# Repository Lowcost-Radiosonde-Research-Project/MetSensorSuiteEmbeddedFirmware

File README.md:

# Met Pico Sensor Suite - Firmware Skeleton

Status as of latest revision. Every module now has a real
implementation - BMI330's carries a significant caveat (see below and
its module docstring) since its register map is unverified.

## File layout

| File              | Status | Notes |
|-------------------|--------|-------|
| `config.py`       | Real   | All pins/addresses/constants in one place. Several `TODO`s remain. |
| `packet.py`       | Real   | Fixed-width binary record format (`PACKET_FORMAT = "<I15fBBBB"`, 68 bytes). |
| `bme280.py`       | Real   | Full Bosch compensation formulas, forced-mode reads. I2C bus 1. |
| `rtd_ads1115.py`  | Real   | Ratiometric RTD read + Callendar-Van Dusen (T >= 0 C only). I2C bus 1. |
| `ms5611.py`       | Real   | PROM calibration + 1st/2nd-order temp/pressure compensation. I2C bus 2. |
| `bmi330.py`       | **Unverified** | Register map guessed from the related BMI323; may not function as intended - see caveat below. I2C bus 2. |
| `gps_neo_m9n.py`  | Real   | NMEA GGA parsing: lat/lon/alt/num_sats/UTC time. |
| `sd_logger.py`    | Real   | Mounts SD, appends `packet.pack_record()` output, periodic flush. |
| `imet_packet.py`  | Real   | Builds the 38-byte iMet-1-RSB GPS+PTU-enhanced downlink frame + CRC-16. |
| `link_uart.py`    | Real   | Frames and sends one 38-byte iMet frame per cycle to the RF Pico over UART. |
| `main.py`         | Real   | Two I2C buses, SD log + iMet frame to RF Pico link, per-sensor fault isolation. |

Every sensor module exposes `init_<name>(i2c, addr)` returning an
object with a `read()` method, and `main.py` wraps each init in
`try/except (OSError, ValueError)` and each read in `try/except
OSError` (the only error read() can raise) so one bad/missing sensor
doesn't take down the loop or the log - it just logs NAN for that field
and a `[WARN]` line to the console.

## Bus layout

- **I2C bus 1** (`I2C1*`): ADS1115 (RTD) + BME280
- **I2C bus 2** (`I2C2*`): MS5611 + BMI330
- **UART** (`GPS_UART_*`): NEO-M9N GPS
- **UART** (`LINK_UART_*`): outbound link to the RF Pico, one framed
  38-byte iMet-1-RSB frame per cycle (see `imet_packet.py` /
  `link_uart.py`)
- **SPI** (`SD_*`): SD card

All pin numbers above are placeholders pending the Tuesday wiring
session - see the `TODO`s in `config.py`.

## BMI330 caveat - documentation lacking, driver may not work as intended

`bmi330.py` is written against the BMI323's register map (a related
Bosch part) because verified BMI330-specific register documentation
wasn't available when this was written. The register addresses,
ACC_CONF/GYR_CONF bitfield values, and full-scale range assumptions are
all unverified guesses. **The driver may run without raising any error
and still return meaningless numbers.**

On Tuesday, `init_bmi330()` will print whatever it reads from the
assumed CHIP_ID register (0x00) as a diagnostic - note that value down.
If accel/gyro readings look like noise, sit constant, or are far
outside physical range (accelerometer magnitude should be close to 1g
at rest), the register map guess is wrong and `bmi330.py` needs
revisiting against real BMI330 documentation (Bosch's BMI3 Sensor API
repo is the best starting point once it covers BMI330). This isn't
blocking for Wednesday - BMI330 isn't part of that test.

## Field naming convention

`packet.FIELD_NAMES` prefixes every field with the sensor that owns it
(`bme280_*`, `ms5611_*`, `rtd_*`, `bmi330_*`, `gps_*`). BMI330 fields
are in milli-g / milli-deg/s (`_mg` / `_mdps`) rather than g / deg-per-s
- worth keeping in mind when the real BMI330 driver is written, since
the conversion from raw counts will need to land in those units.

The GPS record has `gps_num_sats` plus `gps_hour`/`gps_minute`/
`gps_second` (UTC time of fix), but no fix-type field - `gps.read()`
returns a 7-tuple `(lat, lon, alt, num_sats, hour, minute, second)`.
Position/altitude are NAN and the satellite/time fields are
`NO_DATA_U8` until a checksum-valid GGA sentence with a non-zero fix
quality has been parsed. If you want fix-quality (e.g. for
SondeHub-style reporting) added too, that's a small change to
`packet.py` (one more `B` field) and `gps_neo_m9n.py`'s `_parse_gga()`.

## iMet-1-RSB downlink frame

Each cycle, after the SD record is written, `main.py` builds a
separate 38-byte frame via `imet_packet.pack_frame()` - a GPS Data
Packet (`PKT_ID=0x02`, 18 bytes) immediately followed by a PTU
(enhanced) Data Packet (`PKT_ID=0x04`, 20 bytes), each with its own
CRC-16, matching InterMet's "Appendix A - Binary Radiosonde Packet
Definition" as decoded by `imet1rsb`. This frame - not the `packet.py`
record - is what gets sent over `link_uart` to the RF Pico for AFSK
modulation; `packet.py` stays SD-only.

Current sensor -> iMet field mapping (set in `main.py`, easy to
change - it's just which `record[...]` value is passed to which
`imet_packet` keyword argument):

| iMet field | Source | Notes |
|---|---|---|
| GPS lat/lon/alt/num_sats/hour/min/sec | `gps_*` record fields | real NMEA GGA parsing; NAN/NO_DATA until a fix is acquired |
| P (pressure) | `ms5611_pressure_hpa` | **TODO**: confirm vs. BME280 as the primary pressure source |
| T (primary temp) | `bme280_temp_c` | |
| U (humidity) | `bme280_humidity_pct` | |
| Vbat | hardcoded NAN | **TODO**: no battery-voltage sensing exists yet (new ADC channel) |
| Tint (internal temp) | `bme280_temp_c` | **TODO**: currently duplicates T - confirm intent |
| Tpr (probe temp) | `rtd_temp_c` | |
| Tu (aux temp) | hardcoded NAN | **TODO**: no mapping defined - InterMet's intended use of this field is unclear |

All of the NAN/sentinel placeholders above pack safely (verified in
`imet_packet.py`'s `_scaled_*`/`_encode_altitude` helpers - they map
NAN to the field's "no data" value rather than raising), so the frame
is well-formed even with everything still stubbed.

## Before Tuesday (no hardware needed)

- [ ] Get a copy of `sdcard.py` onto the board. Easiest path in
      Thonny/REPL: `import mip; mip.install("sdcard")`. This is the
      standard MicroPython SD-over-SPI block driver - `sd_logger.py`
      imports it as `sdcard`.
- [ ] Skim `config.py` for the `TODO` items - nothing blocks you from
      reading the code now, but these are the values you'll set Tuesday.

## Tuesday, once hardware is in hand

- [ ] Update `config.py` pin numbers for both I2C buses, SPI (SD), GPS
      UART, the RF Pico link UART, and `REGULATOR_EN_PIN` (LM2596 3.3V
      rail enable) to match actual wiring.
- [ ] Confirm `RTD_MUX` / `REF_MUX` (which ADS1115 differential pair is
      the RTD vs. the reference resistor) and `ADS1115_GAIN` (PGA
      setting), based on the RTD interface board.
- [ ] Confirm `MS5611_I2C_ADDR` and `BMI330_I2C_ADDR` once those boards
      are wired. MS5611 and GPS now have real drivers, so a wrong
      address will surface as `[WARN] ... init failed` from
      `_safe_init` rather than silently logging NaN.
- [ ] For BMI330: note the `[INFO] BMI330 CHIP_ID register read as
      0x..` line at startup and sanity-check accel/gyro readings
      against the caveat above - this driver's register map is a
      guess.
- [ ] Run `main.py`. With only BME280 + RTD wired, expect `[WARN]`
      lines at startup for MS5611/BMI330/GPS init or SD mount (if not
      present) - that's expected, the loop should keep running and
      print live T/P/RH/RTD values once per second.

## Wednesday (storm chase)

The console line each cycle:

```
t=   12345ms  T= 23.45C  P=1006.32hPa  RH= 45.2%  RTD= 23.10C
```

gives a live sanity check that BME280 and RTD agree roughly with each
other and with ambient conditions. The SD card (if mounted) accumulates
`PACKET_SIZE`-byte (68-byte) binary records in `/sd/metlog.bin` - decode
with `packet.unpack_record()` in a small post-processing script, reading
`PACKET_SIZE` bytes at a time.

## Known gaps / next steps

- RTD conversion only handles T >= 0 C (Callendar-Van Dusen quadratic
  inversion). The sub-zero cubic-term inversion needs to be added before
  the actual flight.
- BMI330 is unverified - see the dedicated caveat section above and
  `bmi330.py`'s module docstring before trusting any IMU data.
- `link_uart.py` now sends a 38-byte iMet frame instead of the
  65-byte `packet.py` record - see "iMet-1-RSB downlink frame" above
  for the sensor mapping and its open TODOs (Vbat sensing, GPS UTC
  time, P/Tint/Tu assignment).
- `imet_packet.py` matches the field layout and CRC algorithm from
  `imet1rsb.c`'s source, but hasn't been cross-checked byte-for-byte
  against a compiled run of that decoder yet. Worth doing once there's
  a spare moment - compile `imet1rsb.c`, feed it a known frame, and
  confirm its `crc16()` agrees with `imet_packet.crc16()`.
- The RF Pico's receive-side parser for `link_uart`'s frame format
  (sync bytes + length + checksum) doesn't exist yet - that's firmware
  for the other board, out of scope here, but the frame format is
  documented at the top of `link_uart.py` so it can be matched.
- `main.py` currently runs everything on a single core via a simple
  fixed-interval loop. If SD writes, link UART sends, or sensor reads
  start causing timing jitter once everything is real, revisit
  splitting acquisition and logging across the two cores with
  `_thread`.

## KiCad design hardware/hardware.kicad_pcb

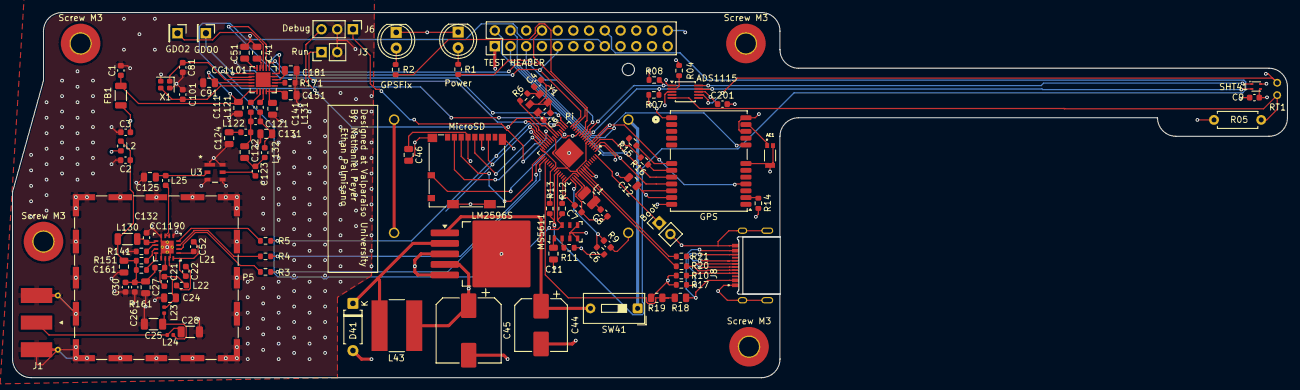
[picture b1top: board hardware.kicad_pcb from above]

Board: 4 copper layers, 206.0 x 59.0 mm, 114 parts (1 on the bottom side), 86 nets.

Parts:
ADS1115: ADS1115IDGS; TSSOP-10_3x3mm_P0.5mm
AE1: W3011; XDCR_W3011
B41: 1079; 1079_KEY
Boot: J_BOOT; PinHeader_1x02_P2.54mm_Vertical
C1, C30: 1uF; C_0603_1608Metric
C2: 10uF; C_0603_1608Metric
C3: 220pF; C_0603_1608Metric
C4, C5: 15p; C_0603_1608Metric
C6, C7, C8: 4.7u; C_0603_1608Metric
C9, C201: 10 uF; C_0603_1608Metric
C11, C12, C46: 0.1 uF; C_0805_2012Metric
C21, C26, C123: 47pF; C_0603_1608Metric
C22, C52, C81: 12pF; C_0603_1608Metric
C24: 3.3pF; C_0805_2012Metric
C25: 7.5pF; C_1206_3216Metric
C27: 1nF; C_0805_2012Metric
C28: DNP; C_1206_3216Metric
C41, C51, C91, C111, C141, C151, C181: 100nF; C_0805_2012Metric
C44: 180 uF; CP_Elec_8x6.7
C45: 330/35 uF/V; CP_Elec_10x10
C101, C132: 15pF; C_0603_1608Metric
C121: 1.9pF; C_0603_1608Metric
C122, C131: 1.5pF; C_0805_2012Metric
C124: 100pF; C_0805_2012Metric
C125: 0.8pF; C_0805_2012Metric
C161: 27pF; C_0805_2012Metric
CC1101: CC1101; Texas_RGP0020H_VQFN-20-1EP_4x4mm_P0.5mm_EP2.4x2.4mm_Thermal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
CC1190: CC1190; RGV0016A
D41: 1N5820; D_A-405_P7.62mm_Horizontal
FB1: FerriteBead; L_1206_3216Metric
GDO0, GDO2: TestPoint; PinHeader_1x01_P2.54mm_Vertical
GPS: NEO-M9N; ublox_NEO
GPSFix: Blue LED; LED_D5.0mm
J1: SMA; SMA_Molex_73251-1153_EdgeMount_Horizontal
J3: J_RUN; PinHeader_1x02_P2.54mm_Vertical
J6: DEBUG; PinHeader_1x03_P2.54mm_Vertical
J8: GSB1C4621DS1HR; AMPHENOL_GSB1C4621DS1HR
L1: 3.3u; L_1008_2520Metric
L2: 11nH; L_0603_1608Metric
L21: 22nH; L_0603_1608Metric
L22: 7.5nH; L_0603_1608Metric
L23: 2.9nH; L_0402_1005Metric
L24: 9.1nH; L_0402_1005Metric
L25: 10nH; L_0603_1608Metric
L43: 33 uH; L_Bourns-SRN8040_8x8.15mm
L121, L131: 12nH; L_0603_1608Metric
L122, L132: 18nH; L_0603_1608Metric
L130: 1.5nH; L_1206_3216Metric
LM2596S: LM2596S-3.3; TO-263-5_TabPin3
MS5611: MS5611-01BA; LGA-8_3x5mm_P1.25mm
MicroSD: Micro_SD_Card_Det1; microSD_HC_Molex_104031-0811
P5: BMI-S-205-C; Laird_Technologies_BMI-S-203-F_26.21x26.21mm
Pi: RP2354A; QFN-60-1EP_7x7mm_P0.4mm_EP3.4x3.4mm
Power: Red LED; LED_D5.0mm
R1, R2: 330; R_0603_1608Metric
R3, R4, R04, R5: 10K; R_0603_1608Metric
R05: 10K OHM 0.1% 0.4W AXIAL; R_Axial_DIN0207_L6.3mm_D2.5mm_P7.62mm_Horizontal
R6: 1K; R_0603_1608Metric
R07, R08, R12, R13, R15, R16: 4.7k; R_0603_1608Metric
R9: 33; R_0603_1608Metric
R10, R17: 5.1K; R_0603_1608Metric
R11, R14: 10k; R_0603_1608Metric
R18, R19: 27K; R_0805_2012Metric
R20, R21: 27; R_0603_1608Metric
R141: 3.3k; R_0603_1608Metric
R151: 47; R_0603_1608Metric
R161: 10; R_0603_1608Metric
R171: 56K; R_0603_1608Metric
RT1: PPG102JA
SHT41: SHT41-AD1B-R3; SHT4X
SW41: SW_SPST; SW_DIP_SPSTx01_Slide_9.78x4.72mm_W7.62mm_P2.54mm
Screw M3, Screw M3#2, Screw M3#3, Screw M3#4: MountingHole_3.2mm_M3_Pad_TopBottom
TEST HEADER: Test Header; PinHeader_2x12_P2.54mm_Vertical
U3: B39921B3588U410; B39162B3522U410_TDK-L
X1: 26.000 MHz; Crystal_SMD_2016-4Pin_2.0x1.6mm
Y1: CX3225SB12000D0GZJC1; OSCCC320X250X60N

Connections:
GPS_EXT_INT: GPS.4 (EXTINT), Pi.5 (GPIO3), TEST HEADER.5
GPS_RESET_N: GPS.8 (~RESET), Pi.4 (GPIO2), TEST HEADER.4
GPS_RX: GPS.20 (TXD/SPI_MISO), Pi.3 (GPIO1), TEST HEADER.3
GPS_TX: GPS.21 (RXD/SPI_MOSI), Pi.2 (GPIO0), TEST HEADER.2
HGM: Pi.33 (GPIO21), R3.2, TEST HEADER.17
I2C0_SCL: ADS1115.10 (SCL), Pi.8 (GPIO5), R08.2, SHT41.1 (SDA), TEST HEADER.7
I2C0_SDA: ADS1115.9 (SDA), Pi.7 (GPIO4), R07.2, SHT41.2 (SCL), TEST HEADER.6
I2C1_SCL: MS5611.8 (SCLK), Pi.40 (GPIO26/ADC0), R13.1, TEST HEADER.16
I2C1_SDA: MS5611.7 (SDI/SDA), Pi.41 (GPIO27/ADC1), R12.1, TEST HEADER.15
LED_GPSF: Pi.10 (GPIO7), R2.2
LED_PWR: Pi.9 (GPIO6), R1.2
LNA_EN: Pi.32 (GPIO20), R4.2, TEST HEADER.18
unnamed: B41.2, B41.4
unnamed: C4.2, R6.1, Y1.3
unnamed: C21.1, C24.1, L22.1, L23.1
unnamed: C22.1, L22.2
unnamed: C25.1, L23.2, L24.1
unnamed: C121.1, C122.1, L121.1, L122.2
unnamed: C121.2, C131.1, L131.1, L132.2
unnamed: C122.2, C123.1, L132.1
unnamed: C123.2, U3.5
unnamed: C124.1, L122.1
unnamed: C125.1, L25.2, U3.2
unnamed: C2.1, C26.1, C27.1, C30.1, C161.1, L2.1, L21.1, L130.1, R151.1, R161.1
unnamed: Power.2 (A), R1.1
unnamed: GPSFix.2 (A), R2.1
unnamed: D41.1 (K), L43.2, LM2596S.2 (OUT)
unnamed: C28.1, J1.1 (In), L24.2
unnamed: J8.A5 (CC1), R10.1
unnamed: J8.B5 (CC2), R17.1
unnamed: J8.A7 (DN1), J8.B7 (DN2), R20.1
unnamed: J8.A6 (DP1), J8.B6 (DP2), R21.1
unnamed: J8.A4_B9 (VBUS_A), J8.B4_A9 (VBUS_B), R18.1
unnamed: ADS1115.5 (AIN1), R05.2, RT1.1 (IN)
unnamed: B41.1, SW41.1 (A)
unnamed: C44.1, LM2596S.1 (VIN), SW41.2 (B)
unnamed: C6.2, Pi.46 (VREG_AVDD), R9.1
unnamed: CC1190.14 (BIAS), R141.2
unnamed: CC1190.6 (HGM), R3.1
unnamed: CC1190.7 (LNA_EN), R4.1
unnamed: C52.2, CC1190.5 (LNA_IN)
unnamed: CC1190.10 (LNA_OUT), CC1190.11 (PA_IN), L25.1
unnamed: CC1190.8 (PA_EN), R5.1
unnamed: C21.2, CC1190.2 (PA_OUT), L21.2
unnamed: C22.2, C52.1, CC1190.4 (TR_SW)
unnamed: C132.1, CC1190.13 (VDD_LNA), L130.2
unnamed: CC1190.16 (VDD_PA1), R161.2
unnamed: CC1190.15 (VDD_PA2), R151.2
unnamed: ADS1115.2 (ALERT/RDY), R04.2
unnamed: C51.1, CC1101.5 (DCOUPL)
unnamed: C1.1, C41.1, C91.1, C111.1, C141.1, C151.1, C181.1, CC1101.4 (DVDD), CC1101.9 (AVDD), CC1101.11 (AVDD), CC1101.14 (AVDD), CC1101.15 (AVDD), CC1101.18 (DGUARD), FB1.1
unnamed: CC1101.6 (GDO0), GDO0.1 (1_1)
unnamed: CC1101.3 (GDO2), GDO2.1 (1_1)
unnamed: CC1101.17 (RBIAS), R171.1
unnamed: CC1101.13 (RF_N), L131.2
unnamed: CC1101.12 (RF_P), L121.2
unnamed: C81.1, CC1101.8 (XOSC_Q1), X1.1
unnamed: C101.1, CC1101.10 (XOSC_Q2), X1.2
unnamed: MS5611.2 (PS), R11.1
unnamed: GPS.2 (D_SEL), R14.2
unnamed: AE1.1, GPS.11 (RF_IN)
unnamed: GPS.19 (SCL/SPI_CLK), R16.2
unnamed: GPS.18 (SDA/~SPI_CS), R15.2
PA_EN: Pi.18 (GPIO14), R5.2, TEST HEADER.12
QSPI_SS: Boot.1, Pi.60 (~QSPI_SS)
RUN: J3.1, Pi.26 (RUN)
SD_CSn: MicroSD.2 (DAT3/CD), Pi.28 (GPIO17), TEST HEADER.21
SD_DETECT: MicroSD.9 (DET), Pi.19 (GPIO15), TEST HEADER.23
SD_RX: MicroSD.7 (DAT0), Pi.27 (GPIO16), TEST HEADER.22
SD_SCK: MicroSD.5 (CLK), Pi.29 (GPIO18), TEST HEADER.20
SD_TX: MicroSD.3 (CMD), Pi.31 (GPIO19), TEST HEADER.19
SPI1_CSn: CC1101.7 (CSN), Pi.17 (GPIO13), TEST HEADER.11
SPI1_RX: CC1101.2 (SO), Pi.16 (GPIO12), TEST HEADER.10
SPI1_SCK: CC1101.1 (SCLK), Pi.14 (GPIO10), TEST HEADER.8
SPI1_TX: CC1101.20 (SI), Pi.15 (GPIO11), TEST HEADER.9
SWCLK: J6.1, Pi.24 (SWCLK)
SWDIO: J6.3, Pi.25 (SWDIO)
USB_DM: Pi.51 (USB_DM), R20.2
USB_DP: Pi.52 (USB_DP), R21.2
VBUS: Pi.34 (GPIO22), R18.2, R19.1
VREG_FB: C8.2, L1.1, Pi.6 (DVDD), Pi.23 (DVDD), Pi.39 (DVDD), Pi.50 (VREG_FB)
VREG_LX: L1.2, Pi.48 (VREG_LX)
VREG_PGND: ADS1115.1 (ADDR), ADS1115.3 (GND), ADS1115.7 (AIN3), AE1.2, AE1.3, B41.3, Boot.2, C1.2, C2.2, C3.2, C4.1, C5.1, C6.1, C7.1, C8.1, C9.2, C11.2, C12.2, C24.2, C25.2, C26.2, C27.2, C28.2, C30.2, C41.2, C44.2, C45.2, C46.2, C51.2, C81.2, C91.2, C101.2, C111.2, C124.2, C125.2, C131.2, C132.2, C141.2, C151.2, C161.2, C181.2, C201.2, CC1101.16 (GND), CC1101.19 (GND), CC1101.21 (EPAD), CC1190.1 (GND), CC1190.3 (GND), CC1190.9 (GND), CC1190.12 (GND), CC1190.17 (GND), D41.2 (A), GPS.7 (VDD_USB), GPS.10 (GND), GPS.12 (GND), GPS.13 (GND), GPS.24 (GND), GPSFix.1 (K), J1.2 (Ext), J3.2, J6.2, J8.A1_B12 (GND_A), J8.B1_A12 (GND_B), J8.SH1 (SHIELD), J8.SH2 (SHIELD__1), J8.SH3 (SHIELD__2), J8.SH4 (SHIELD__3), LM2596S.3 (GND), LM2596S.5 (~ON/OFF), MS5611.3 (GND), MS5611.4 (CSB), MS5611.5 (CSB), MicroSD.6 (VSS), MicroSD.SH (SHIELD), P5.1 (Shield_1), Pi.47 (VREG_PGND), Pi.61 (GND), Power.1 (K), R10.2, R17.2, R19.2, R141.1, R171.2, RT1.2 (OUT), SHT41.4 (VSS), TEST HEADER.13, TEST HEADER.14, TEST HEADER.24, U3.1, U3.3, U3.4, U3.6, Y1.2 (GND), Y1.4 (GND__1)
VREG_VIN: ADS1115.8 (VDD), C3.1, C7.2, C9.1, C11.1, C12.1, C45.1, C46.1, C201.1, FB1.2, GPS.22 (V_BCKP), GPS.23 (VCC), L2.2, L43.1, LM2596S.4 (FB), MS5611.1 (VDD), MicroSD.4 (VDD), Pi.1 (IOVDD), Pi.11 (IOVDD), Pi.20 (IOVDD), Pi.30 (IOVDD), Pi.38 (IOVDD), Pi.44 (ADC_AVDD), Pi.45 (IOVDD), Pi.49 (VREG_VIN), Pi.53 (USB_OTP_VDD), Pi.54 (QSPI_IOVDD), R04.1, R05.1, R07.1, R08.1, R9.2, R11.2, R12.2, R13.2, R14.1, R15.1, R16.1, SHT41.3 (VDD), TEST HEADER.1
XIN: C5.2, Pi.21 (XIN), Y1.1
XOUT: Pi.22 (XOUT), R6.2

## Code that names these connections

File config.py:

"""Hardware configuration constants for the Met Pico sensor suite.

Centralizes pin assignments, bus addresses, ADC channel mappings, and
calibration constants so that hardware changes only require edits in
this file. Values marked TODO are placeholders pending hardware
confirmation and must be updated before flight.

Author: Nathaniel Peyer
Date: 06-14-2026
"""

# I2C bus 1: ADS1115 (RTD interface) and BME280.
I2C1 = 0
I2C1_SDA_PIN = 0
I2C1_SCL_PIN = 1
I2C1_FREQ_HZ = 400000

# I2C bus 2: MS5611 and BMI330.
# TODO: confirm BMI330 is on I2C (vs SPI) once hardware is finalized -
# this assumes both remaining I2C sensors share the second bus.
I2C2 = 1
I2C2_SDA_PIN = 2
I2C2_SCL_PIN = 3
I2C2_FREQ_HZ = 400000

# BME280 (temperature / pressure / humidity).
BME280_I2C_ADDR = 0x76

# MS5611 (high-resolution pressure / temperature).
# TODO: confirm address (0x77 if CSB tied high, 0x76 if tied low).
MS5611_I2C_ADDR = 0x77

# BMI330 (6-axis IMU).
# TODO: confirm address and bus once hardware is finalized.
BMI330_I2C_ADDR = 0x68

# ADS1115 (4-wire PT1000 RTD interface).
ADS1115_I2C_ADDR = 0x48

# ADS1115 MUX[2:0] codes (config register bits 14:12) select which
# differential pair is measured. The ADS1115 only supports four
# differential combinations:
#   0b000 -> AIN0 - AIN1
#   0b001 -> AIN0 - AIN3
#   0b010 -> AIN1 - AIN3
#   0b011 -> AIN2 - AIN3
# TODO: confirm which pair carries the RTD sense voltage and which
# carries the reference resistor once the RTD interface board wiring
# is finalized.
RTD_MUX = 0b000
REF_MUX = 0b011

# ADS1115 PGA[2:0] code (config register bits 11:9) sets the full-scale
# input range:
#   0 -> +/-6.144V   1 -> +/-4.096V   2 -> +/-2.048V
#   3 -> +/-1.024V   4 -> +/-0.512V   5 -> +/-0.256V
# TODO: confirm once excitation current and the expected voltage range
# across the RTD and reference resistor are known.
ADS1115_GAIN = 1

RTD_REF_RESISTANCE_OHMS = 10000.0

# Callendar-Van Dusen coefficients for PT1000 (IEC 60751), valid for
# T >= 0 deg C.
RTD_R0_OHMS = 1000.0
RTD_CVD_A = 3.9083e-3
RTD_CVD_B = -5.775e-7

# NEO-M9N GPS (UART, NMEA 0183).
GPS_UART_ID = 1
GPS_UART_TX_PIN = 4
GPS_UART_RX_PIN = 5
GPS_UART_BAUD_RATE = 9600

# UART link to the RF Pico - one packet.pack_record() payload, framed
# by link_uart.send_record(), is sent each sample cycle.
# TODO: confirm pins and baud rate once the inter-Pico wiring is set.
LINK_UART_ID = 0
LINK_UART_TX_PIN = 12
LINK_UART_RX_PIN = 13
LINK_UART_BAUD_RATE = 115200

# SD card (SPI).
SD_SPI_ID = 0
SD_SCK_PIN = 18
SD_MOSI_PIN = 19
SD_MISO_PIN = 16
SD_CS_PIN = 17
SD_MOUNT_POINT = "/sd"
SD_LOG_FILENAME = "/sd/metlog.bin"

# LM2596 switching regulator that supplies the 3.3V sensor rail. This
# GPIO must be driven high before any I2C/UART sensor transaction will
# succeed - main() asserts it first thing, then waits
# REGULATOR_ENABLE_DELAY_MS for the rail to settle.
# TODO: confirm pin number once wiring is finalized.
REGULATOR_EN_PIN = 14
REGULATOR_ENABLE_DELAY_MS = 50

# Sampling and logging cadence.
SAMPLE_INTERVAL_MS = 1000
SD_FLUSH_INTERVAL_SAMPLES = 5

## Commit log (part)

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2026-06-14 Created the repo for the project and set up admin files - NWP
2026-06-14 Started Main.py
2026-06-15 Added packet.py and config.py - NWP
2026-06-15 restructured repo and added more sensor drivers - NWP
2026-06-15 Added more drivers and fixed all present VSCode errors. - NWP
2026-06-15 Change project title in README.md
    Updated project title and removed old title from README.
2026-06-17 Chase Mode Activated - NWP
2026-06-19 Working on fixing the RTD and other sensor readings. - NWP
2026-06-20 Fixed pin mapping for the new hardware. - NWP

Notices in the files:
README.md:
License: BSD 3-Clause
